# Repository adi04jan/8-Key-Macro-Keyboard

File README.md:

# Macro Keyboard

This project was build to provide a convinent way to control some basic task while working. Also this was a way for me to explore CH551G a wonderfull IC with so much potential.
Although the code is still a bit messy but it does what it is supposed to do.

The project was build around in a weekend so maybe some parts are not polished and may have a lot of bugs but what can we get in a weekend right !

I had a CNC milling machine lying around so I made a simple PCB with lowest possible jumpers and lowest necessary components to make the PCB in single side and with minimum assembley.

PCB Files are located inside `Macro Mini Keypad PCB Files`
and Source code is in `8xMacro_Keypad_main/8xMain_key`

## Code

Before programming the CH551G please follow [this guide](https://github.com/DeqingSun/ch55xduino "this guide") .

Once the Arduino is configured to compile code for ch551G go to `tools > User setting > 148B USB RAM` and slect this setting.

Now you can compile and upload the code in the Board via USB just remember to keep pressed the mini button behind the USB connetor while connecting the USB cable.

### Touch Switch config

There are 2 touch switch that need to be wired externally which can change the keyboard modes. 
For initial code it only change the copy paste command as in Linux terminal normal `ctrl + c `doesnt work but `ctrl + shift + c ` work.

in the 3D file behind the arrows a simple copper tap can be stuck and using wire can be connected to the pin 2 and 3 of the CH551G to change mode UP and Down.

### Changing the Keypress

Keypress can be changed in the attached Key_config.h file .
just replace the segment inside the function `Keyboard_press(   );` with what ever keypress you want to perform.
all the key press command are listed below

```

#define KEY_LEFT_CTRL   0x80
#define KEY_LEFT_SHIFT    0x81
#define KEY_LEFT_ALT    0x82
#define KEY_LEFT_GUI    0x83
#define KEY_RIGHT_CTRL    0x84
#define KEY_RIGHT_SHIFT   0x85
#define KEY_RIGHT_ALT   0x86
#define KEY_RIGHT_GUI   0x87

#define KEY_UP_ARROW    0xDA
#define KEY_DOWN_ARROW    0xD9
#define KEY_LEFT_ARROW    0xD8
#define KEY_RIGHT_ARROW   0xD7
#define KEY_BACKSPACE   0xB2
#define KEY_TAB       0xB3
#define KEY_RETURN      0xB0
#define KEY_ESC       0xB1
#define KEY_INSERT      0xD1
#define KEY_DELETE      0xD4
#define KEY_PAGE_UP     0xD3
#define KEY_PAGE_DOWN   0xD6
#define KEY_HOME      0xD2
#define KEY_END       0xD5
#define KEY_CAPS_LOCK   0xC1
#define KEY_F1        0xC2
#define KEY_F2        0xC3
#define KEY_F3        0xC4
#define KEY_F4        0xC5
#define KEY_F5        0xC6
#define KEY_F6        0xC7
#define KEY_F7        0xC8
#define KEY_F8        0xC9
#define KEY_F9        0xCA
#define KEY_F10       0xCB
#define KEY_F11       0xCC
#define KEY_F12       0xCD
#define KEY_F13       0xF0
#define KEY_F14       0xF1
#define KEY_F15       0xF2
#define KEY_F16       0xF3
#define KEY_F17       0xF4
#define KEY_F18       0xF5
#define KEY_F19       0xF6
#define KEY_F20       0xF7
#define KEY_F21       0xF8
#define KEY_F22       0xF9
#define KEY_F23       0xFA
#define KEY_F24       0xFB

 CONSUMER_POWER    = 0x30,
    CONSUMER_SLEEP = 0x32,
    
    MEDIA_RECORD = 0xB2,
    MEDIA_FAST_FORWARD    = 0xB3,
    MEDIA_REWIND    = 0xB4,
    MEDIA_NEXT    = 0xB5,
    MEDIA_PREVIOUS    = 0xB6,
    MEDIA_PREV    = 0xB6, // Alias
    MEDIA_STOP    = 0xB7,
    MEDIA_PLAY_PAUSE    = 0xCD,
    MEDIA_PAUSE    = 0xB0,
    
    MEDIA_VOLUME_MUTE    = 0xE2,
    MEDIA_VOL_MUTE = 0xE2, // Alias
    MEDIA_VOLUME_UP    = 0xE9,
    MEDIA_VOL_UP    = 0xE9, // Alias
    MEDIA_VOLUME_DOWN    = 0xEA,
    MEDIA_VOL_DOWN    = 0xEA, // Alias
    
    CONSUMER_BRIGHTNESS_UP = 0x006F,
    CONSUMER_BRIGHTNESS_DOWN = 0x0070,
    
    CONSUMER_SCREENSAVER = 0x19e,
    
    CONSUMER_PROGRAMMABLE_BUTTON_CONFIGURATION = 0x182,
    CONSUMER_CONTROL_CONFIGURATION = 0x183,
    CONSUMER_EMAIL_READER    = 0x18A,
    CONSUMER_CALCULATOR    = 0x192,
    CONSUMER_EXPLORER    = 0x194,
    
    CONSUMER_BROWSER_HOME    = 0x223,
    CONSUMER_BROWSER_BACK    = 0x224,
    CONSUMER_BROWSER_FORWARD    = 0x225,
    CONSUMER_BROWSER_REFRESH    = 0x227,
    CONSUMER_BROWSER_BOOKMARKS    = 0x22A,

    // Consumer_Page_(0x0C)    0x15
    HID_CONSUMER_UNASSIGNED        = 0x00,
    HID_CONSUMER_NUMERIC_KEY_PAD    = 0x02,    // HID type NARY
    HID_CONSUMER_PROGRAMMABLE_BUTTONS    = 0x03,    // HID type NARY
    HID_CONSUMER_MICROPHONE_CA    = 0x04,
    HID_CONSUMER_HEADPHONE_CA    = 0x05,
    HID_CONSUMER_GRAPHIC_EQUALIZER_CA    = 0x06,
    // Reserved    = 0x07-1F
    HID_CONSUMER_PLUS_10    = 0x20,    // HID type OSC
    HID_CONSUMER_PLUS_100    = 0x21,    // HID type OSC
    HID_CONSUMER_AM_SLASH_PM    = 0x22,    // HID type OSC
    // Reserved    = 0x23-3F
    HID_CONSUMER_POWER    = 0x30,    // HID type OOC
    HID_CONSUMER_RESET    = 0x31,    // HID type OSC
    HID_CONSUMER_SLEEP    = 0x32,    // HID type OSC
    HID_CONSUMER_SLEEP_AFTER    = 0x33,    // HID type OSC
    HID_CONSUMER_SLEEP_MODE    = 0x34,    // HID type RTC
    HID_CONSUMER_ILLUMINATION    = 0x35,    // HID type OOC
    HID_CONSUMER_FUNCTION_BUTTONS    = 0x36,    // HID type NARY
    // Reserved    = 0x37-3F
    HID_CONSUMER_MENU    = 0x40,    // HID type OOC
    HID_CONSUMER_MENU_PICK    = 0x41,    // HID type OSC
    HID_CONSUMER_MENU_UP    = 0x42,    // HID type OSC
    HID_CONSUMER_MENU_DOWN    = 0x43,    // HID type OSC
    HID_CONSUMER_MENU_LEFT    = 0x44,    // HID type OSC
    HID_CONSUMER_MENU_RIGHT    = 0x45,    // HID type OSC
    HID_CONSUMER_MENU_ESCAPE    = 0x46,    // HID type OSC
    HID_CONSUMER_MENU_VALUE_INCREASE    = 0x47,    // HID type OSC
    HID_CONSUMER_MENU_VALUE_DECREASE    = 0x48,    // HID type OSC
    // Reserved 0x49-5F
    HID_CONSUMER_DATA_ON_SCREEN    = 0x60,    // HID type OOC
    HID_CONSUMER_CLOSED_CAPTION    = 0x61,    // HID type OOC
    HID_CONSUMER_CLOSED_CAPTION_SELECT    = 0x62,    // HID type OSC
    HID_CONSUMER_VCR_SLASH_TV    = 0x63,    // HID type OOC
    HID_CONSUMER_BROADCAST_MODE    = 0x64,    // HID type OSC
    HID_CONSUMER_SNAPSHOT    = 0x65,    // HID type OSC
    HID_CONSUMER_STILL    = 0x66,    // HID type OSC
    // Reserved 0x67-7F
    HID_CONSUMER_SELECTION    = 0x80,    // HID type NARY
    HID_CONSUMER_ASSIGN_SELECTION    = 0x81,    // HID type OSC
    HID_CONSUMER_MODE_STEP    = 0x82,    // HID type OSC
    HID_CONSUMER_RECALL_LAST    = 0x83,    // HID type OSC
    HID_CONSUMER_ENTER_CHANNEL    = 0x84,    // HID type OSC
    HID_CONSUMER_ORDER_MOVIE    = 0x85,    // HID type OSC
    HID_CONSUMER_CHANNEL    = 0x86,    // HID type LC
    HID_CONSUMER_MEDIA_SELECTION    = 0x87,    // HID type NARY
    HID_CONSUMER_MEDIA_SELECT_COMPUTER    = 0x88,    // HID type SEL
    HID_CONSUMER_MEDIA_SELECT_TV    = 0x89,    // HID type SEL
    HID_CONSUMER_MEDIA_SELECT_WWW    = 0x8A,    // HID type SEL
    HID_CONSUMER_MEDIA_SELECT_DVD    = 0x8B,    // HID type SEL
    HID_CONSUMER_MEDIA_SELECT_TELEPHONE    = 0x8C,    // HID type SEL
    HID_CONSUMER_MEDIA_SELECT_PROGRAM_GUIDE    = 0x8D,    // HID type SEL
    HID_CONSUMER_MEDIA_SELECT_VIDEO_PHONE    = 0x8E,    // HID type SEL
    HID_CONSUMER_MEDIA_SELECT_GAMES    = 0x8F,    // HID type SEL
    HID_CONSUMER_MEDIA_SELECT_MESSAGES    = 0x90,    // HID type SEL
    HID_CONSUMER_MEDIA_SELECT_CD    = 0x91,    // HID type SEL
    HID_CONSUMER_MEDIA_SELECT_VCR    = 0x92,    // HID type SEL
    HID_CONSUMER_MEDIA_SELECT_TUNER    = 0x93,    // HID type SEL
    HID_CONSUMER_QUIT    = 0x94,    // HID type OSC
    HID_CONSUMER_HELP    = 0x95,    // HID type OOC
    HID_CONSUMER_MEDIA_SELECT_TAPE    = 0x96,    // HID type SEL
    HID_CONSUMER_MEDIA_SELECT_CABLE    = 0x97,    // HID type SEL
    HID_CONSUMER_MEDIA_SELECT_SATELLITE    = 0x98,    // HID type SEL
    HID_CONSUMER_MEDIA_SELECT_SECURITY    = 0x99,    // HID type SEL
    HID_CONSUMER_MEDIA_SELECT_HOME    = 0x9A,    // HID type SEL
    HID_CONSUMER_MEDIA_SELECT_CALL    = 0x9B,    // HID type SEL
    HID_CONSUMER_CHANNEL_INCREMENT    = 0x9C,    // HID type OSC
    HID_CONSUMER_CHANNEL_DECREMENT    = 0x9D,    // HID type OSC
    HID_CONSUMER_MEDIA_SELECT_SAP    = 0x9E,    // HID type SEL
    // Reserved 0x9F
    HID_CONSUMER_VCR_PLUS    = 0xA0,    // HID type OSC
    HID_CONSUMER_ONCE    = 0xA1,    // HID type OSC
    HID_CONSUMER_DAILY    = 0xA2,    // HID type OSC
    HID_CONSUMER_WEEKLY    = 0xA3,    // HID type OSC
    HID_CONSUMER_MONTHLY    = 0xA4,    // HID type OSC
    // Reserved 0xA5-AF
    HID_CONSUMER_PLAY    = 0xB0,    // HID type OOC
    HID_CONSUMER_PAUSE    = 0xB1,    // HID type OOC
    HID_CONSUMER_RECORD    = 0xB2,    // HID type OOC
    HID_CONSUMER_FAST_FORWARD    = 0xB3,    // HID type OOC
    HID_CONSUMER_REWIND    = 0xB4,    // HID type OOC
    HID_CONSUMER_SCAN_NEXT_TRACK    = 0xB5,    // HID type OSC
    HID_CONSUMER_SCAN_PREVIOUS_TRACK    = 0xB6,    // HID type OSC
    HID_CONSUMER_STOP    = 0xB7,    // HID type OSC
    HID_CONSUMER_EJECT    = 0xB8,    // HID type OSC
    HID_CONSUMER_RANDOM_PLAY    = 0xB9,    // HID type OOC
    HID_CONSUMER_SELECT_DISC    = 0xBA,    // HID type NARY
    HID_CONSUMER_ENTER_DISC_MC    = 0xBB,
    HID_CONSUMER_REPEAT    = 0xBC,    // HID type OSC
    HID_CONSUMER_TRACKING    = 0xBD,    // HID type LC
    HID_CONSUMER_TRACK_NORMAL    = 0xBE,    // HID type OSC
    HID_CONSUMER_SLOW_TRACKING    = 0xBF,    // HID type LC
    HID_CONSUMER_FRAME_FORWARD    = 0xC0,    // HID type RTC
    HID_CONSUMER_FRAME_BACK    = 0xC1,    // HID type RTC
    HID_CONSUMER_MARK    = 0xC2,    // HID type OSC
    HID_CONSUMER_CLEAR_MARK    = 0xC3,    // HID type OSC
    HID_CONSUMER_REPEAT_FROM_MARK    = 0xC4,    // HID type OOC
    HID_CONSUMER_RETURN_TO_MARK    = 0xC5,    // HID type OSC
    HID_CONSUMER_SEARCH_MARK_FORWARD    = 0xC6,    // HID type OSC
    HID_CONSUMER_SEARCH_MARK_BACKWARDS    = 0xC7,    // HID type OSC
    HID_CONSUMER_COUNTER_RESET    = 0xC8,    // HID type OSC
    HID_CONSUMER_SHOW_COUNTER    = 0xC9,    // HID type OSC
    HID_CONSUMER_TRACKING_INCREMENT    = 0xCA,    // HID type RTC
    HID_CONSUMER_TRACKING_DECREMENT    = 0xCB,    // HID type RTC
    HID_CONSUMER_STOP_SLASH_EJECT    = 0xCC,    // HID type OSC
    HID_CONSUMER_PLAY_SLASH_PAUSE    = 0xCD,    // HID type OSC
    HID_CONSUMER_PLAY_SLASH_SKIP    = 0xCE,    // HID type OSC
    // Reserved 0xCF-DF
    HID_CONSUMER_VOLUME    = 0xE0,    // HID type LC
    HID_CONSUMER_BALANCE    = 0xE1,    // HID type LC
    HID_CONSUMER_MUTE    = 0xE2,    // HID type OOC
    HID_CONSUMER_BASS    = 0xE3,    // HID type LC
    HID_CONSUMER_TREBLE    = 0xE4,    // HID type LC
    HID_CONSUMER_BASS_BOOST    = 0xE5,    // HID type OOC
    HID_CONSUMER_SURROUND_MODE    = 0xE6,    // HID type OSC
    HID_CONSUMER_LOUDNESS    = 0xE7,    // HID type OOC
    HID_CONSUMER_MPX    = 0xE8,    // HID type OOC
    HID_CONSUMER_VOLUME_INCREMENT    = 0xE9,    // HID type RTC
    HID_CONSUMER_VOLUME_DECREMENT    = 0xEA,    // HID type RTC
    // Reserved 0xEB-EF
    HID_CONSUMER_SPEED_SELECT    = 0xF0,    // HID type OSC
    HID_CONSUMER_PLAYBACK_SPEED    = 0xF1,    // HID type NARY
    HID_CONSUMER_STANDARD_PLAY    = 0xF2,    // HID type SEL
    HID_CONSUMER_LONG_PLAY    = 0xF3,    // HID type SEL
    HID_CONSUMER_EXTENDED_PLAY    = 0xF4,    // HID type SEL
    HID_CONSUMER_SLOW    = 0xF5,    // HID type OSC
    // Reserved 0xF6-FF
    HID_CONSUMER_FAN_ENABLE    = 0x100,    // HID type OOC
    HID_CONSUMER_FAN_SPEED    = 0x101,    // HID type LC
    HID_CONSUMER_LIGHT_ENABLE    = 0x102,    // HID type OOC
    HID_CONSUMER_LIGHT_ILLUMINATION_LEVEL    = 0x103,    // HID type LC
    HID_CONSUMER_CLIMATE_CONTROL_ENABLE    = 0x104,    // HID type OOC
    HID_CONSUMER_ROOM_TEMPERATURE    = 0x105,    // HID type LC
    HID_CONSUMER_SECURITY_ENABLE    = 0x106,    // HID type OOC
    HID_CONSUMER_FIRE_ALARM    = 0x107,    // HID type OSC
    HID_CONSUMER_POLICE_ALARM    = 0x108,    // HID type OSC
    HID_CONSUMER_PROXIMITY    = 0x109,    // HID type LC
    HID_CONSUMER_MOTION    = 0x10A,    // HID type OSC
    HID_CONSUMER_DURESS_ALARM    = 0x10B,    // HID type OSC
    HID_CONSUMER_HOLDUP_ALARM    = 0x10C,    // HID type OSC
    HID_CONSUMER_MEDICAL_ALARM    = 0x10D,    // HID type OSC
    // Reserved 0x10E-14F
    HID_CONSUMER_BALANCE_RIGHT    = 0x150,    // HID type RTC
    HID_CONSUMER_BALANCE_LEFT    = 0x151,    // HID type RTC
    HID_CONSUMER_BASS_INCREMENT    = 0x152,    // HID type RTC
    HID_CONSUMER_BASS_DECREMENT    = 0x153,    // HID type RTC
    HID_CONSUMER_TREBLE_INCREMENT    = 0x154,    // HID type RTC
    HID_CONSUMER_TREBLE_DECREMENT    = 0x155,    // HID type RTC
    // Reserved 0x156-15F
    HID_CONSUMER_SPEAKER_SYSTEM    = 0x160,    // HID type CL
    HID_CONSUMER_CHANNEL_LEFT    = 0x161,    // HID type CL
    HID_CONSUMER_CHANNEL_RIGHT    = 0x162,    // HID type CL
    HID_CONSUMER_CHANNEL_CENTER    = 0x163,    // HID type CL
    HID_CONSUMER_CHANNEL_FRONT    = 0x164,    // HID type CL
    HID_CONSUMER_CHANNEL_CENTER_FRONT    = 0x165,    // HID type CL
    HID_CONSUMER_CHANNEL_SIDE    = 0x166,    // HID type CL
    HID_CONSUMER_CHANNEL_SURROUND    = 0x167,    // HID type CL
    HID_CONSUMER_CHANNEL_LOW_FREQUENCY_ENHANCEMENT    = 0x168,    // HID type CL
    HID_CONSUMER_CHANNEL_TOP    = 0x169,    // HID type CL
    HID_CONSUMER_CHANNEL_UNKNOWN    = 0x16A,    // HID type CL
    // Reserved 0x16B-16F
    HID_CONSUMER_SUB_CHANNEL    = 0x170,    // HID type LC
    HID_CONSUMER_SUB_CHANNEL_INCREMENT    = 0x171,    // HID type OSC
    HID_CONSUMER_SUB_CHANNEL_DECREMENT    = 0x172,    // HID type OSC
    HID_CONSUMER_ALTERNATE_AUDIO_INCREMENT    = 0x173,    // HID type OSC
    HID_CONSUMER_ALTERNATE_AUDIO_DECREMENT    = 0x174,    // HID type OSC
    // Reserved 0x175-17F
    HID_CONSUMER_APPLICATION_LAUNCH_BUTTONS    = 0x180,    // HID type NARY
    HID_CONSUMER_AL_LAUNCH_BUTTON_CONFIGURATION_TOOL    = 0x181,    // HID type SEL
    HID_CONSUMER_AL_PROGRAMMABLE_BUTTON_CONFIGURATION    = 0x182,    // HID type SEL
    HID_CONSUMER_AL_CONSUMER_CONTROL_CONFIGURATION    = 0x183,    // HID type SEL
    HID_CONSUMER_AL_WORD_PROCESSOR    = 0x184,    // HID type SEL
    HID_CONSUMER_AL_TEXT_EDITOR    = 0x185,    // HID type SEL
    HID_CONSUMER_AL_SPREADSHEET    = 0x186,    // HID type SEL
    HID_CONSUMER_AL_GRAPHICS_EDITOR    = 0x187,    // HID type SEL
    HID_CONSUMER_AL_PRESENTATION_APP    = 0x188,    // HID type SEL
    HID_CONSUMER_AL_DATABASE_APP    = 0x189,    // HID type SEL
    HID_CONSUMER_AL_EMAIL_READER    = 0x18A,    // HID type SEL
    HID_CONSUMER_AL_NEWSREADER    = 0x18B,    // HID type SEL
    HID_CONSUMER_AL_VOICEMAIL    = 0x18C,    // HID type SEL
    HID_CONSUMER_AL_CONTACTS_SLASH_ADDRESS_BOOK    = 0x18D,    // HID type SEL
    HID_CONSUMER_AL_CALENDAR_SLASH_SCHEDULE    = 0x18E,    // HID type SEL
    HID_CONSUMER_AL_TASK_SLASH_PROJECT_MANAGER    = 0x18F,    // HID type SEL
    HID_CONSUMER_AL_LOG_SLASH_JOURNAL_SLASH_TIMECARD    = 0x190,    // HID type SEL
    HID_CONSUMER_AL_CHECKBOOK_SLASH_FINANCE    = 0x191,    // HID type SEL
    HID_CONSUMER_AL_CALCULATOR    = 0x192,    // HID type SEL
    HID_CONSUMER_AL_A_SLASH_V_CAPTURE_SLASH_PLAYBACK    = 0x193,    // HID type SEL
    HID_CONSUMER_AL_LOCAL_MACHINE_BROWSER    = 0x194,    // HID type SEL
    HID_CONSUMER_AL_LAN_SLASH_WAN_BROWSER    = 0x195,    // HID type SEL
    HID_CONSUMER_AL_INTERNET_BROWSER    = 0x196,    // HID type SEL
    HID_CONSUMER_AL_REMOTE_NETWORKING_SLASH_ISP_CONNECT    = 0x197,    // HID type SEL
    HID_CONSUMER_AL_NETWORK_CONFERENCE    = 0x198,    // HID type SEL
    HID_CONSUMER_AL_NETWORK_CHAT    = 0x199,    // HID type SEL
    HID_CONSUMER_AL_TELEPHONY_SLASH_DIALER    = 0x19A,    // HID type SEL
    HID_CONSUMER_AL_LOGON    = 0x19B,    // HID type SEL
    HID_CONSUMER_AL_LOGOFF    = 0x19C,    // HID type SEL
    HID_CONSUMER_AL_LOGON_SLASH_LOGOFF    = 0x19D,    // HID type SEL
    HID_CONSUMER_AL_TERMINAL_LOCK_SLASH_SCREENSAVER    = 0x19E,    // HID type SEL
    HID_CONSUMER_AL_CONTROL_PANEL    = 0x19F,    // HID type SEL
    HID_CONSUMER_AL_COMMAND_LINE_PROCESSOR_SLASH_RUN    = 0x1A0,    // HID type SEL
    HID_CONSUMER_AL_PROCESS_SLASH_TASK_MANAGER    = 0x1A1,    // HID type SEL
    HID_CONSUMER_AL_SELECT_TASK_SLASH_APPLICATION    = 0x1A2,    // HID type SEL
    HID_CONSUMER_AL_NEXT_TASK_SLASH_APPLICATION    = 0x1A3,    // HID type SEL
    HID_CONSUMER_AL_PREVIOUS_TASK_SLASH_APPLICATION    = 0x1A4,    // HID type SEL
    HID_CONSUMER_AL_PREEMPTIVE_HALT_TASK_SLASH_APPLICATION    = 0x1A5,    // HID type SEL
    HID_CONSUMER_AL_INTEGRATED_HELP_CENTER    = 0x1A6,    // HID type SEL
    HID_CONSUMER_AL_DOCUMENTS    = 0x1A7,    // HID type SEL
    HID_CONSUMER_AL_THESAURUS    = 0x1A8,    // HID type SEL
    HID_CONSUMER_AL_DICTIONARY    = 0x1A9,    // HID type SEL
    HID_CONSUMER_AL_DESKTOP    = 0x1AA,    // HID type SEL
    HID_CONSUMER_AL_SPELL_CHECK    = 0x1AB,    // HID type SEL
    HID_CONSUMER_AL_GRAMMAR_CHECK    = 0x1AC,    // HID type SEL
    HID_CONSUMER_AL_WIRELESS_STATUS    = 0x1AD,    // HID type SEL
    HID_CONSUMER_AL_KEYBOARD_LAYOUT    = 0x1AE,    // HID type SEL
    HID_CONSUMER_AL_VIRUS_PROTECTION    = 0x1AF,    // HID type SEL
    HID_CONSUMER_AL_ENCRYPTION    = 0x1B0,    // HID type SEL
    HID_CONSUMER_AL_SCREEN_SAVER    = 0x1B1,    // HID type SEL
    HID_CONSUMER_AL_ALARMS    = 0x1B2,    // HID type SEL
    HID_CONSUMER_AL_CLOCK    = 0x1B3,    // HID type SEL
    HID_CONSUMER_AL_FILE_BROWSER    = 0x1B4,    // HID type SEL
    HID_CONSUMER_AL_POWER_STATUS    = 0x1B5,    // HID type SEL
    HID_CONSUMER_AL_IMAGE_BROWSER    = 0x1B6,    // HID type SEL
    HID_CONSUMER_AL_AUDIO_BROWSER    = 0x1B7,    // HID type SEL
    HID_CONSUMER_AL_MOVIE_BROWSER    = 0x1B8,    // HID type SEL
    HID_CONSUMER_AL_DIGITAL_RIGHTS_MANAGER    = 0x1B9,    // HID type SEL
    HID_CONSUMER_AL_DIGITAL_WALLET    = 0x1BA,    // HID type SEL
    // _Reserved 0x1BB
    HID_CONSUMER_AL_INSTANT_MESSAGING    = 0x1BC,    // HID type SEL
    HID_CONSUMER_AL_OEM_FEATURES_SLASH__TIPS_SLASH_TUTORIAL_BROWSER    = 0x1BD,    // HID type SEL
    HID_CONSUMER_AL_OEM_HELP    = 0x1BE,    // HID type SEL
    HID_CONSUMER_AL_ONLINE_COMMUNITY    = 0x1BF,    // HID type SEL
    HID_CONSUMER_AL_ENTERTAINMENT_CONTENT_BROWSER    = 0x1C0,    // HID type SEL
    HID_CONSUMER_AL_ONLINE_SHOPPING_BROWSER    = 0x1C1,    // HID type SEL
    HID_CONSUMER_AL_SMARTCARD_INFORMATION_SLASH_HELP    = 0x1C2,    // HID type SEL
    HID_CONSUMER_AL_MARKET_MONITOR_SLASH_FINANCE_BROWSER    = 0x1C3,    // HID type SEL
    HID_CONSUMER_AL_CUSTOMIZED_CORPORATE_NEWS_BROWSER    = 0x1C4,    // HID type SEL
    HID_CONSUMER_AL_ONLINE_ACTIVITY_BROWSER    = 0x1C5,    // HID type SEL
    HID_CONSUMER_AL_RESEARCH_SLASH_SEARCH_BROWSER    = 0x1C6,    // HID type SEL
    HID_CONSUMER_AL_AUDIO_PLAYER    = 0x1C7,    // HID type SEL
    // Reserved 0x1C8-1FF
    HID_CONSUMER_GENERIC_GUI_APPLICATION_CONTROLS    = 0x200, // HID type NARY
    HID_CONSUMER_AC_NEW    = 0x201,    // HID type SEL
    HID_CONSUMER_AC_OPEN    = 0x202,    // HID type SEL
    HID_CONSUMER_AC_CLOSE    = 0x203,    // HID type SEL
    HID_CONSUMER_AC_EXIT    = 0x204,    // HID type SEL
    HID_CONSUMER_AC_MAXIMIZE    = 0x205,    // HID type SEL
    HID_CONSUMER_AC_MINIMIZE    = 0x206,    // HID type SEL
    HID_CONSUMER_AC_SAVE    = 0x207,    // HID type SEL
    HID_CONSUMER_AC_PRINT    = 0x208,    // HID type SEL
    HID_CONSUMER_AC_PROPERTIES    = 0x209,    // HID type SEL
    HID_CONSUMER_AC_UNDO    = 0x21A,    // HID type SEL
    HID_CONSUMER_AC_COPY    = 0x21B,    // HID type SEL
    HID_CONSUMER_AC_CUT    = 0x21C,    // HID type SEL
    HID_CONSUMER_AC_PASTE    = 0x21D,    // HID type SEL
    HID_CONSUMER_AC_SELECT_ALL    = 0x21E,    // HID type SEL
    HID_CONSUMER_AC_FIND    = 0x21F,    // HID type SEL
    HID_CONSUMER_AC_FIND_AND_REPLACE    = 0x220,    // HID type SEL
    HID_CONSUMER_AC_SEARCH    = 0x221,    // HID type SEL
    HID_CONSUMER_AC_GO_TO    = 0x222,    // HID type SEL
    HID_CONSUMER_AC_HOME    = 0x223,    // HID type SEL
    HID_CONSUMER_AC_BACK    = 0x224,    // HID type SEL
    HID_CONSUMER_AC_FORWARD    = 0x225,    // HID type SEL
    HID_CONSUMER_AC_STOP    = 0x226,    // HID type SEL
    HID_CONSUMER_AC_REFRESH    = 0x227,    // HID type SEL
    HID_CONSUMER_AC_PREVIOUS_LINK    = 0x228,    // HID type SEL
    HID_CONSUMER_AC_NEXT_LINK    = 0x229,    // HID type SEL
    HID_CONSUMER_AC_BOOKMARKS    = 0x22A,    // HID type SEL
    HID_CONSUMER_AC_HISTORY    = 0x22B,    // HID type SEL
    HID_CONSUMER_AC_SUBSCRIPTIONS    = 0x22C,    // HID type SEL
    HID_CONSUMER_AC_ZOOM_IN    = 0x22D,    // HID type SEL
    HID_CONSUMER_AC_ZOOM_OUT    = 0x22E,    // HID type SEL
    HID_CONSUMER_AC_ZOOM    = 0x22F,    // HID type LC
    HID_CONSUMER_AC_FULL_SCREEN_VIEW    = 0x230,    // HID type SEL
    HID_CONSUMER_AC_NORMAL_VIEW    = 0x231,    // HID type SEL
    HID_CONSUMER_AC_VIEW_TOGGLE    = 0x232,    // HID type SEL
    HID_CONSUMER_AC_SCROLL_UP    = 0x233,    // HID type SEL
    HID_CONSUMER_AC_SCROLL_DOWN    = 0x234,    // HID type SEL
    HID_CONSUMER_AC_SCROLL    = 0x235,    // HID type LC
    HID_CONSUMER_AC_PAN_LEFT    = 0x236,    // HID type SEL
    HID_CONSUMER_AC_PAN_RIGHT    = 0x237,    // HID type SEL
    HID_CONSUMER_AC_PAN    = 0x238,    // HID type LC
    HID_CONSUMER_AC_NEW_WINDOW    = 0x239,    // HID type SEL
    HID_CONSUMER_AC_TILE_HORIZONTALLY    = 0x23A,    // HID type SEL
    HID_CONSUMER_AC_TILE_VERTICALLY    = 0x23B,    // HID type SEL
    HID_CONSUMER_AC_FORMAT    = 0x23C,    // HID type SEL
    HID_CONSUMER_AC_EDIT    = 0x23D,    // HID type SEL
    HID_CONSUMER_AC_BOLD    = 0x23E,    // HID type SEL
    HID_CONSUMER_AC_ITALICS    = 0x23F,    // HID type SEL
    HID_CONSUMER_AC_UNDERLINE    = 0x240,    // HID type SEL
    HID_CONSUMER_AC_STRIKETHROUGH    = 0x241,    // HID type SEL
    HID_CONSUMER_AC_SUBSCRIPT    = 0x242,    // HID type SEL
    HID_CONSUMER_AC_SUPERSCRIPT    = 0x243,    // HID type SEL
    HID_CONSUMER_AC_ALL_CAPS    = 0x244,    // HID type SEL
    HID_CONSUMER_AC_ROTATE    = 0x245,    // HID type SEL
    HID_CONSUMER_AC_RESIZE    = 0x246,    // HID type SEL
    HID_CONSUMER_AC_FLIP_HORIZONTAL    = 0x247,    // HID type SEL
    HID_CONSUMER_AC_FLIP_VERTICAL    = 0x248,    // HID type SEL
    HID_CONSUMER_AC_MIRROR_HORIZONTAL    = 0x249,    // HID type SEL
    HID_CONSUMER_AC_MIRROR_VERTICAL    = 0x24A,    // HID type SEL
    HID_CONSUMER_AC_FONT_SELECT    = 0x24B,    // HID type SEL
    HID_CONSUMER_AC_FONT_COLOR    = 0x24C,    // HID type SEL
    HID_CONSUMER_AC_FONT_SIZE    = 0x24D,    // HID type SEL
    HID_CONSUMER_AC_JUSTIFY_LEFT    = 0x24E,    // HID type SEL
    HID_CONSUMER_AC_JUSTIFY_CENTER_H    = 0x24F,    // HID type SEL
    HID_CONSUMER_AC_JUSTIFY_RIGHT    = 0x250,    // HID type SEL
    HID_CONSUMER_AC_JUSTIFY_BLOCK_H    = 0x251,    // HID type SEL
    HID_CONSUMER_AC_JUSTIFY_TOP    = 0x252,    // HID type SEL
    HID_CONSUMER_AC_JUSTIFY_CENTER_V    = 0x253,    // HID type SEL
    HID_CONSUMER_AC_JUSTIFY_BOTTOM    = 0x254,    // HID type SEL
    HID_CONSUMER_AC_JUSTIFY_BLOCK_V    = 0x255,    // HID type SEL
    HID_CONSUMER_AC_INDENT_DECREASE    = 0x256,    // HID type SEL
    HID_CONSUMER_AC_INDENT_INCREASE    = 0x257,    // HID type SEL
    HID_CONSUMER_AC_NUMBERED_LIST    = 0x258,    // HID type SEL
    HID_CONSUMER_AC_RESTART_NUMBERING    = 0x259,    // HID type SEL
    HID_CONSUMER_AC_BULLETED_LIST    = 0x25A,    // HID type SEL
    HID_CONSUMER_AC_PROMOTE    = 0x25B,    // HID type SEL
    HID_CONSUMER_AC_DEMOTE    = 0x25C,    // HID type SEL
    HID_CONSUMER_AC_YES    = 0x25D,    // HID type SEL
    HID_CONSUMER_AC_NO    = 0x25E,    // HID type SEL
    HID_CONSUMER_AC_CANCEL    = 0x25F,    // HID type SEL
    HID_CONSUMER_AC_CATALOG    = 0x260,    // HID type SEL
    HID_CONSUMER_AC_BUY_SLASH_CHECKOUT    = 0x261,    // HID type SEL
    HID_CONSUMER_AC_ADD_TO_CART    = 0x262,    // HID type SEL
    HID_CONSUMER_AC_EXPAND    = 0x263,    // HID type SEL
    HID_CONSUMER_AC_EXPAND_ALL    = 0x264,    // HID type SEL
    HID_CONSUMER_AC_COLLAPSE    = 0x265,    // HID type SEL
    HID_CONSUMER_AC_COLLAPSE_ALL    = 0x266,    // HID type SEL
    HID_CONSUMER_AC_PRINT_PREVIEW    = 0x267,    // HID type SEL
    HID_CONSUMER_AC_PASTE_SPECIAL    = 0x268,    // HID type SEL
    HID_CONSUMER_AC_INSERT_MODE    = 0x269,    // HID type SEL
    HID_CONSUMER_AC_DELETE    = 0x26A,    // HID type SEL
    HID_CONSUMER_AC_LOCK    = 0x26B,    // HID type SEL
    HID_CONSUMER_AC_UNLOCK    = 0x26C,    // HID type SEL
    HID_CONSUMER_AC_PROTECT    = 0x26D,    // HID type SEL
    HID_CONSUMER_AC_UNPROTECT    = 0x26E,    // HID type SEL
    HID_CONSUMER_AC_ATTACH_COMMENT    = 0x26F,    // HID type SEL
    HID_CONSUMER_AC_DELETE_COMMENT    = 0x270,    // HID type SEL
    HID_CONSUMER_AC_VIEW_COMMENT    = 0x271,    // HID type SEL
    HID_CONSUMER_AC_SELECT_WORD    = 0x272,    // HID type SEL
    HID_CONSUMER_AC_SELECT_SENTENCE    = 0x273,    // HID type SEL
    HID_CONSUMER_AC_SELECT_PARAGRAPH    = 0x274,    // HID type SEL
    HID_CONSUMER_AC_SELECT_COLUMN    = 0x275,    // HID type SEL
    HID_CONSUMER_AC_SELECT_ROW    = 0x276,    // HID type SEL
    HID_CONSUMER_AC_SELECT_TABLE    = 0x277,    // HID type SEL
    HID_CONSUMER_AC_SELECT_OBJECT    = 0x278,    // HID type SEL
    HID_CONSUMER_AC_REDO_SLASH_REPEAT    = 0x279,    // HID type SEL
    HID_CONSUMER_AC_SORT    = 0x27A,    // HID type SEL
    HID_CONSUMER_AC_SORT_ASCENDING    = 0x27B,    // HID type SEL
    HID_CONSUMER_AC_SORT_DESCENDING    = 0x27C,    // HID type SEL
    HID_CONSUMER_AC_FILTER    = 0x27D,    // HID type SEL
    HID_CONSUMER_AC_SET_CLOCK    = 0x27E,    // HID type SEL
    HID_CONSUMER_AC_VIEW_CLOCK    = 0x27F,    // HID type SEL
    HID_CONSUMER_AC_SELECT_TIME_ZONE    = 0x280,    // HID type SEL
    HID_CONSUMER_AC_EDIT_TIME_ZONES    = 0x281,    // HID type SEL
    HID_CONSUMER_AC_SET_ALARM    = 0x282,    // HID type SEL
    HID_CONSUMER_AC_CLEAR_ALARM    = 0x283,    // HID type SEL
    HID_CONSUMER_AC_SNOOZE_ALARM    = 0x284,    // HID type SEL
    HID_CONSUMER_AC_RESET_ALARM    = 0x285,    // HID type SEL
    HID_CONSUMER_AC_SYNCHRONIZE    = 0x286,    // HID type SEL
    HID_CONSUMER_AC_SEND_SLASH_RECEIVE    = 0x287,    // HID type SEL
    HID_CONSUMER_AC_SEND_TO    = 0x288,    // HID type SEL
    HID_CONSUMER_AC_REPLY    = 0x289,    // HID type SEL
    HID_CONSUMER_AC_REPLY_ALL    = 0x28A,    // HID type SEL
    HID_CONSUMER_AC_FORWARD_MSG    = 0x28B,    // HID type SEL
    HID_CONSUMER_AC_SEND    = 0x28C,    // HID type SEL
    HID_CONSUMER_AC_ATTACH_FILE    = 0x28D,    // HID type SEL
    HID_CONSUMER_AC_UPLOAD    = 0x28E,    // HID type SEL
    HID_CONSUMER_AC_DOWNLOAD_SAVE_TARGET_AS    = 0x28F,    // HID type SEL
    HID_CONSUMER_AC_SET_BORDERS    = 0x290,    // HID type SEL
    HID_CONSUMER_AC_INSERT_ROW    = 0x291,    // HID type SEL
    HID_CONSUMER_AC_INSERT_COLUMN    = 0x292,    // HID type SEL
    HID_CONSUMER_AC_INSERT_FILE    = 0x293,    // HID type SEL
    HID_CONSUMER_AC_INSERT_PICTURE    = 0x294,    // HID type SEL
    HID_CONSUMER_AC_INSERT_OBJECT    = 0x295,    // HID type SEL
    HID_CONSUMER_AC_INSERT_SYMBOL    = 0x296,    // HID type SEL
    HID_CONSUMER_AC_SAVE_AND_CLOSE    = 0x297,    // HID type SEL
    HID_CONSUMER_AC_RENAME    = 0x298,    // HID type SEL
    HID_CONSUMER_AC_MERGE    = 0x299,    // HID type SEL
    HID_CONSUMER_AC_SPLIT    = 0x29A,    // HID type SEL
    HID_CONSUMER_AC_DISRIBUTE_HORIZONTALLY    = 0x29B,    // HID type SEL
    HID_CONSUMER_AC_DISTRIBUTE_VERTICALLY    = 0x29C,    // HID type SEL

```

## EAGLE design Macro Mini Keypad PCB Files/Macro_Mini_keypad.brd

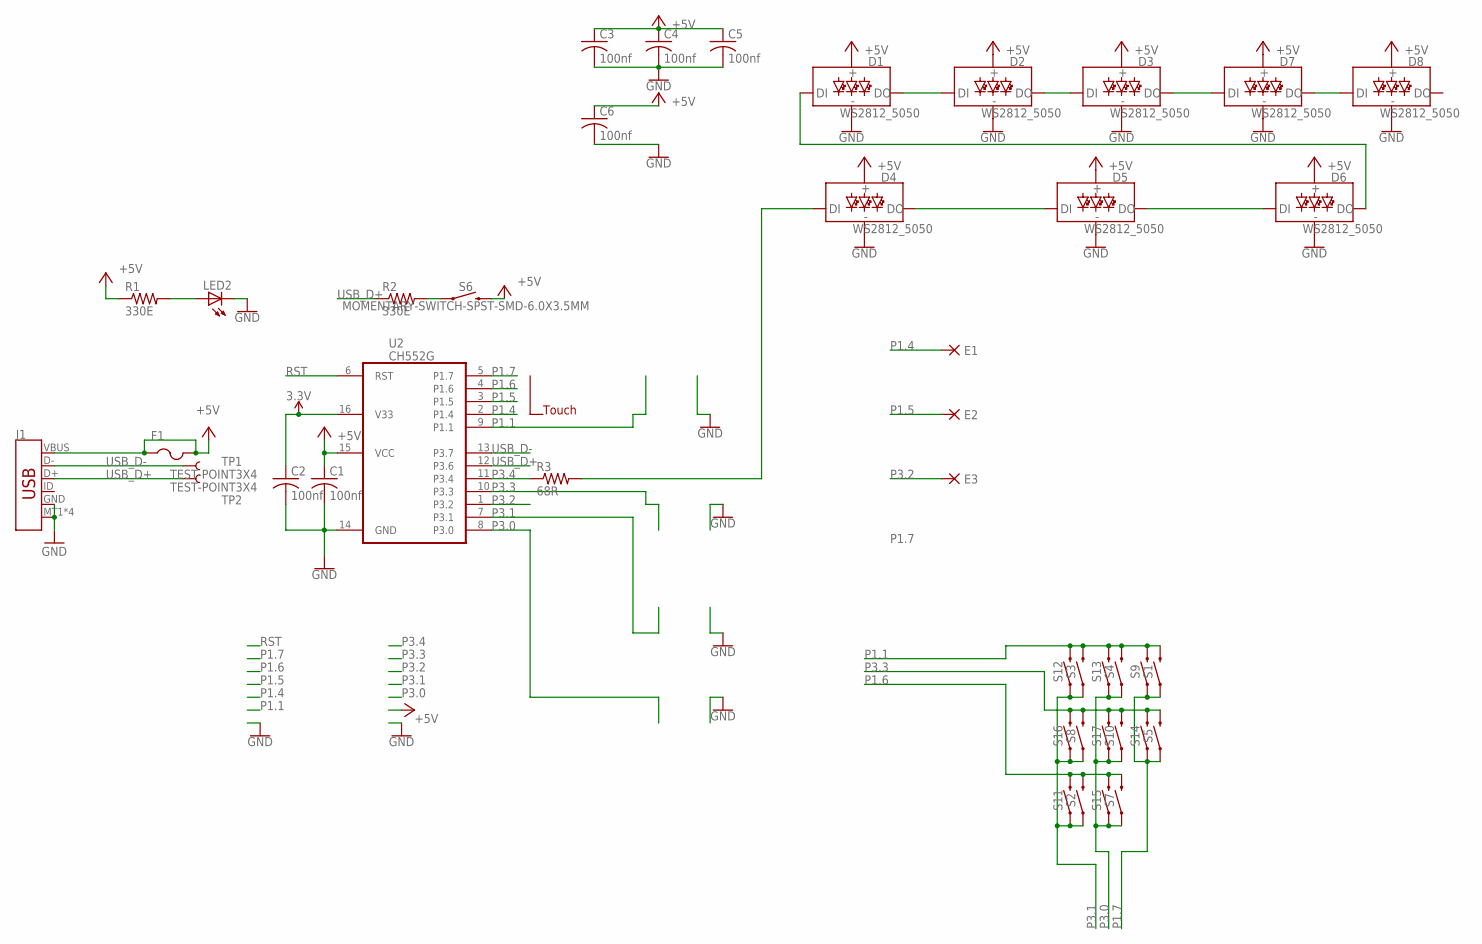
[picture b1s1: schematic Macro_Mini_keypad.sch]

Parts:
C1, C2, C3, C4, C5, C6: 100nf; C1206
D1, D2, D3, D4, D5, D6, D7, D8: WS2812_5050; WS2812-5X5-4PIN
E1, E2, E3: DPADS_PAD-0400-S; DPADS_0400-S
F1: PTCFUSE-1206; R1206; LCSC C151162
J1: USB_MICRO-B_SMT; USB-MICROB
LED2: LEDCHIPLED_1206; CHIPLED_1206
R1, R2: 330E; R1206
R3: 68R; R1206
S1, S2, S3, S4, S5, S7, S8, S10: MECHANICAL-KEYBOARD_CUSTOM1U; CHERRY-MX-LED-1U
S6: MOMENTARY-SWITCH-SPST-SMD-6.0X3.5MM; TACTILE_SWITCH_SMD_6.0X3.5MM
S9, S11, S12, S13, S14, S15, S16, S17: MOMENTARY-SWITCH-SPST-PTH-12MM; TACTILE_SWITCH_PTH_12MM
TP1, TP2: TEST-POINT3X4; PAD.03X.04
U2: CH552G; MY_IC_SO16; LCSC C111292

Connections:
3.3V: C2.1, U2.16 (V33)
+5V: C1.1, C3.1, C4.1, C5.1, C6.1, D1.VCC, D2.VCC, D3.VCC, D4.VCC, D5.VCC, D6.VCC, D7.VCC, D8.VCC, F1.1, F1.2, J1.VBUS, R1.1, S6.2, U2.15 (VCC)
GND: C1.2, C2.2, C3.2, C4.2, C5.2, C6.2, D1.GND, D2.GND, D3.GND, D4.GND, D5.GND, D6.GND, D7.GND, D8.GND, J1.GND, J1.MT1 (SHIELD), J1.MT2 (SHIELD), J1.P$1 (SHIELD), J1.P$2 (SHIELD), LED2.C, U2.14 (GND)
unnamed: R2.2, S6.1
unnamed: D4.DI, R3.2
unnamed: LED2.A, R1.2
unnamed: D4.DO, D5.DI
unnamed: D5.DO, D6.DI
unnamed: D1.DI, D6.DO
unnamed: D1.DO, D2.DI
unnamed: D2.DO, D3.DI
unnamed: D3.DO, D7.DI
unnamed: D7.DO, D8.DI
P1.1: S1.S2 (2), S3.S2 (2), S4.S2 (2), S9.3 (2), S12.3 (2), S13.3 (2), U2.9 (P1.1)
P1.4: E1.PAD, U2.2 (P1.4)
P1.5: E2.PAD, U2.3 (P1.5)
P1.6: S2.S2 (2), S7.S2 (2), S11.3 (2), S15.3 (2), U2.4 (P1.6)
P1.7: S1.S1 (1), S5.S1 (1), S9.1, S14.1, U2.5 (P1.7)
P3.0: S4.S1 (1), S7.S1 (1), S10.S1 (1), S13.1, S15.1, S17.1, U2.8 (P3.0)
P3.1: S2.S1 (1), S3.S1 (1), S8.S1 (1), S11.1, S12.1, S16.1, U2.7 (P3.1)
P3.2: E3.PAD, U2.1 (P3.2)
P3.3: S5.S2 (2), S8.S2 (2), S10.S2 (2), S14.3 (2), S16.3 (2), S17.3 (2), U2.10 (P3.3)
P3.4: R3.1, U2.11 (P3.4)
RST: U2.6 (RST)
USB_D+: J1.D+, R2.1, TP2.P$1, U2.12 (P3.6)
USB_D-: J1.D-, TP1.P$1, U2.13 (P3.7)

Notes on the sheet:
Touch

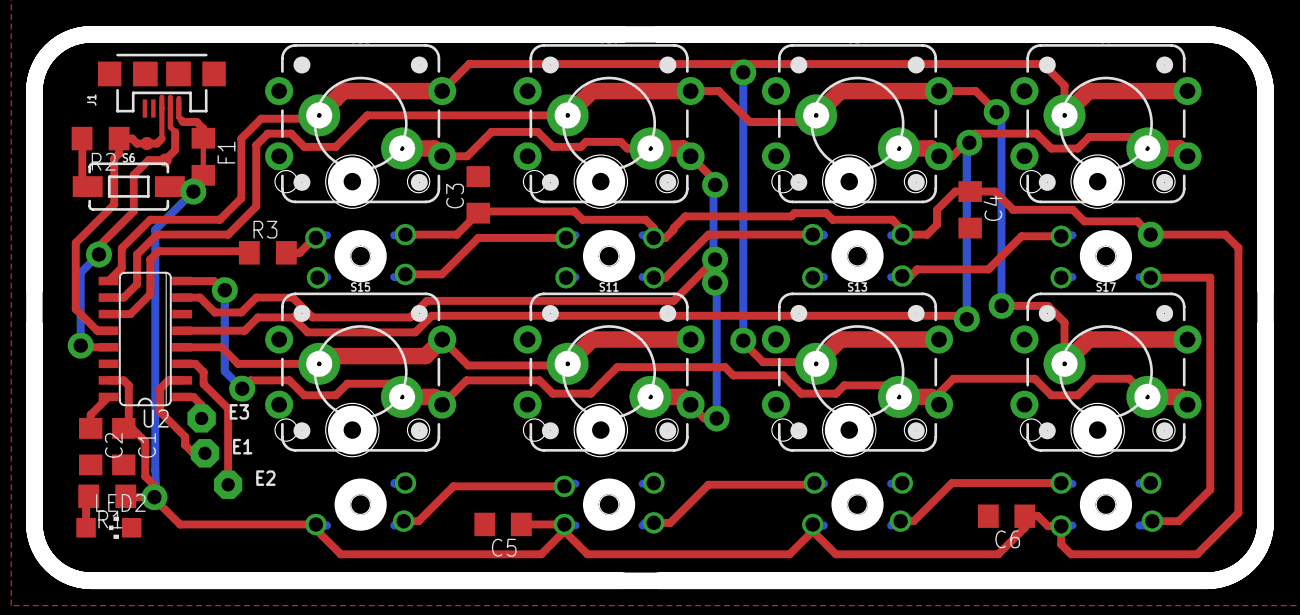
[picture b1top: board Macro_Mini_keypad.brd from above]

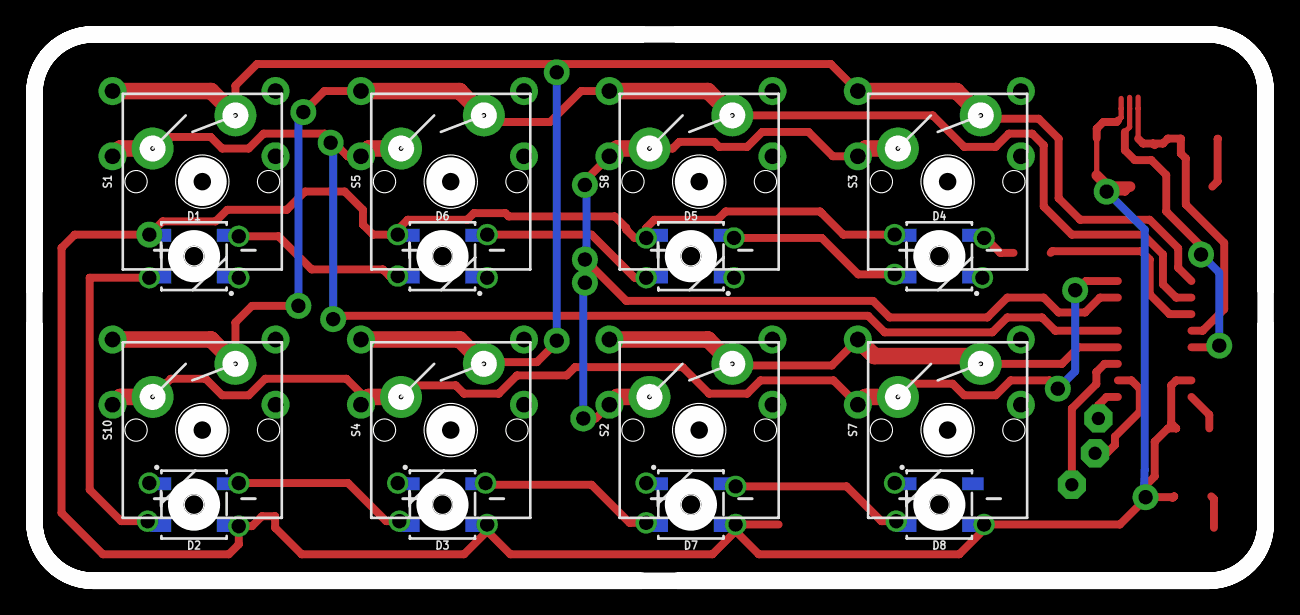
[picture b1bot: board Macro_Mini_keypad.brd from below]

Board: 2 copper layers, 94.4 x 41.9 mm, 43 parts (16 on the bottom side), 25 nets.

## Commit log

2022-10-04 source files added
2022-10-09 Updated sourceCode
2022-10-09 added multiple configuration
2022-10-09 paste speed increase

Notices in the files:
parts and their libraries:
SparkFun-LED: Licensing: Creative Commons ShareAlike 4.0 International - https://creativecommons.org/licenses/by-sa/4.0
SparkFun: Licensing: CC v3.0 Share-Alike You are welcome to use this library for commercial purposes.
